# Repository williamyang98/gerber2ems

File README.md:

# gerber2ems - openEMS simulation based on Gerber files

Copyright (c) 2023 [Antmicro](https://www.antmicro.com)

Modified (c) 2025 [williamyang98](https://github.com/williamyang98)

This project aims to streamline signal integrity simulations using open source tools.
It takes PCB production files as input (Gerber, drill files, stackup information) and simulates trace SI performance using openEMS - a free and open electromagnetic field solver that uses the FDTD method.

This has been forked from [antmicro/gerber2ems](https://github.com/antmicro/gerber2ems) to add:
- Comprehensive documentation.
- Configuration of nanomesh.
- Fixes to nanomesh which resulted in missing or merged copper traces.
- Control over input and output directories.
- Correction of xy offset in simulation port and vias via configuration file.
- Embedding of copper layers into dielectric for better modelling of edge side coupling in differential pairs.

## Documentation
Documentation can be found [here](https://williamyang98.github.io/gerber2ems/docs/).

1. [Installation](https://williamyang98.github.io/gerber2ems/docs/installation)
2. [Exporting files](https://williamyang98.github.io/gerber2ems/docs/export_pcb)
3. [Configuration](https://williamyang98.github.io/gerber2ems/docs/configuration)
4. [Running simulation](https://williamyang98.github.io/gerber2ems/docs/running)
5. [Visualise results](https://williamyang98.github.io/gerber2ems/docs/visualise_results)
6. [Visualise geometry](https://williamyang98.github.io/gerber2ems/docs/visualise_geometry)
7. [Visualise fields](https://williamyang98.github.io/gerber2ems/docs/visualise_fields)
8. [Bugs](https://williamyang98.github.io/gerber2ems/docs/bugs)
9. [Tips](https://williamyang98.github.io/gerber2ems/docs/tips)

## Gallery
### Smith chart

### Differential impedance

### Visualising geometry

### Visualising E-fields with Paraview
https://github.com/user-attachments/assets/467630fa-eb7f-4268-b3ea-a0b4997c61ea

*Simulation of differential pair*

https://github.com/user-attachments/assets/b16ab520-ca9b-4d1a-9d2a-7e88ee9ce144

*Simulation of differential pair over hatched ground plane*

## Useful links
- Original project: [antmicro/gerber2ems](https://github.com/antmicro/gerber2ems)
- Youtube tutorial for openEMS and KiCAD: [youtube/panire](https://www.youtube.com/watch?v=VcJqhsbzR3c)

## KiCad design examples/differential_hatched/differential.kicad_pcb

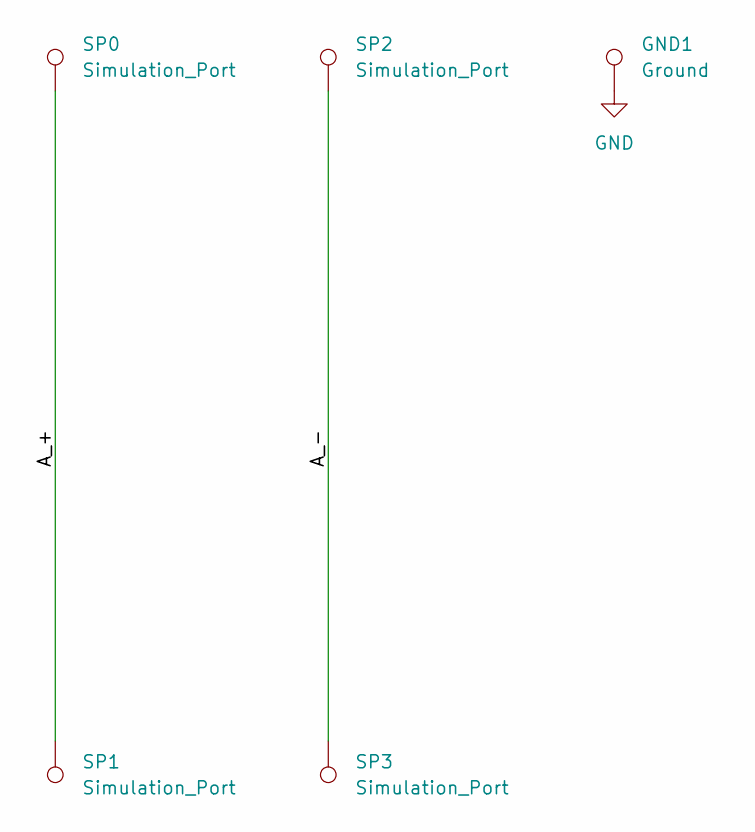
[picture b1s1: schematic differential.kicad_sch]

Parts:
GND1: Ground; pad_0.05mm
SP0, SP1, SP2, SP3: Simulation_Port; pad_0.1mm

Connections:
/A_+: SP0.1, SP1.1
/A_-: SP2.1, SP3.1
GND: GND1.1

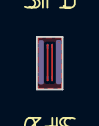
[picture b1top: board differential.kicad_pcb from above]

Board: 2 copper layers, 1.4 x 2.9 mm, 5 parts (0 on the bottom side), 2 nets.

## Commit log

2025-01-29 Huge rewrite to enhance functionality and fix some limitations
    - Allow for selection of input and output folders.
    - Added settings for:
    - Adjusting xy offset of port positions.
    - Settings to control nanomesh quality when converting gerbers to images.
    - Unified 0 indexing for simulation ports in KiCAD schematic and python scripts.
    - Allow adjusting smoothing ratio for mesh lines.
2025-01-30 Improved installation process
2025-01-30 Only install openEMS and CSXCAD from wheel for windows
2025-01-30 Cleaned up configuration file import and added gerbv multiprocessing.
2025-01-30 Create gh-pages
2025-01-30 deploy: 2bb93181363b46249b48caa5bf875e4e6b57817f
2025-01-30 Added hugo docs
2025-01-30 deploy: 6e0e08c82e490f1627fb8bee3d484709e35543e9
2025-01-30 Cleanup docs
2025-01-30 deploy: ee6ad10784c4daf860f4660d350c2184bc7bcb5d
2025-01-30 Added CI for install and running gerber2ems on Windows
2025-01-30 Fix bug in impedance calculation
2025-01-31 Let user backup input and config files manually
2025-01-31 deploy: 99d0f03661e2e3eb2f54b517c397549bdbd4cd59
2025-01-31 Make sure all mesh lines and layers are aligned to integer microns so infinitely flat metal layers dont get misaligned
2025-01-31 Refactor port positioning and document bugs
2025-01-31 Update examples with corrected settings and keep track of exported gerbers
2025-01-31 Keep track of component position files
2025-02-01 Separate out image conversion as a separate step
2025-02-01 deploy: 668370ffe5e92b7d9d5fc189d6d8e41f4f543dfe
2025-02-01 Differential simulation is fast enough to include as part of CI
2025-02-01 Store post processed data and render graphs separately
2025-02-01 Update docs
2025-02-01 deploy: 0580aebecefd790306f47035a63a9b92ac9faab5
2025-02-01 Split up CI into each gerber2ems pipeline step
2025-02-01 Added retry script in CI to deal with openEMS randomly seg faulting
2025-02-01 Use better nanomesh settings by default
2025-02-01 deploy: c5284bce374a9eaee563cca681a29d43a53e0963
2025-02-02 Fixed parsing error with smoothing ratio
2025-02-02 Removed inconsistent and unuseful border offset
2025-02-02 Removed jetson orin example which is missing footprints
2025-02-04 Compensate for KiCAD mirroring of bottom side exported components
